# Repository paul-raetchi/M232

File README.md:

# M232
RS-232 => GPIO Level Translator for 6-CH UART monitoring (3xRX + 3xTX). VCC = 3-6V to GND

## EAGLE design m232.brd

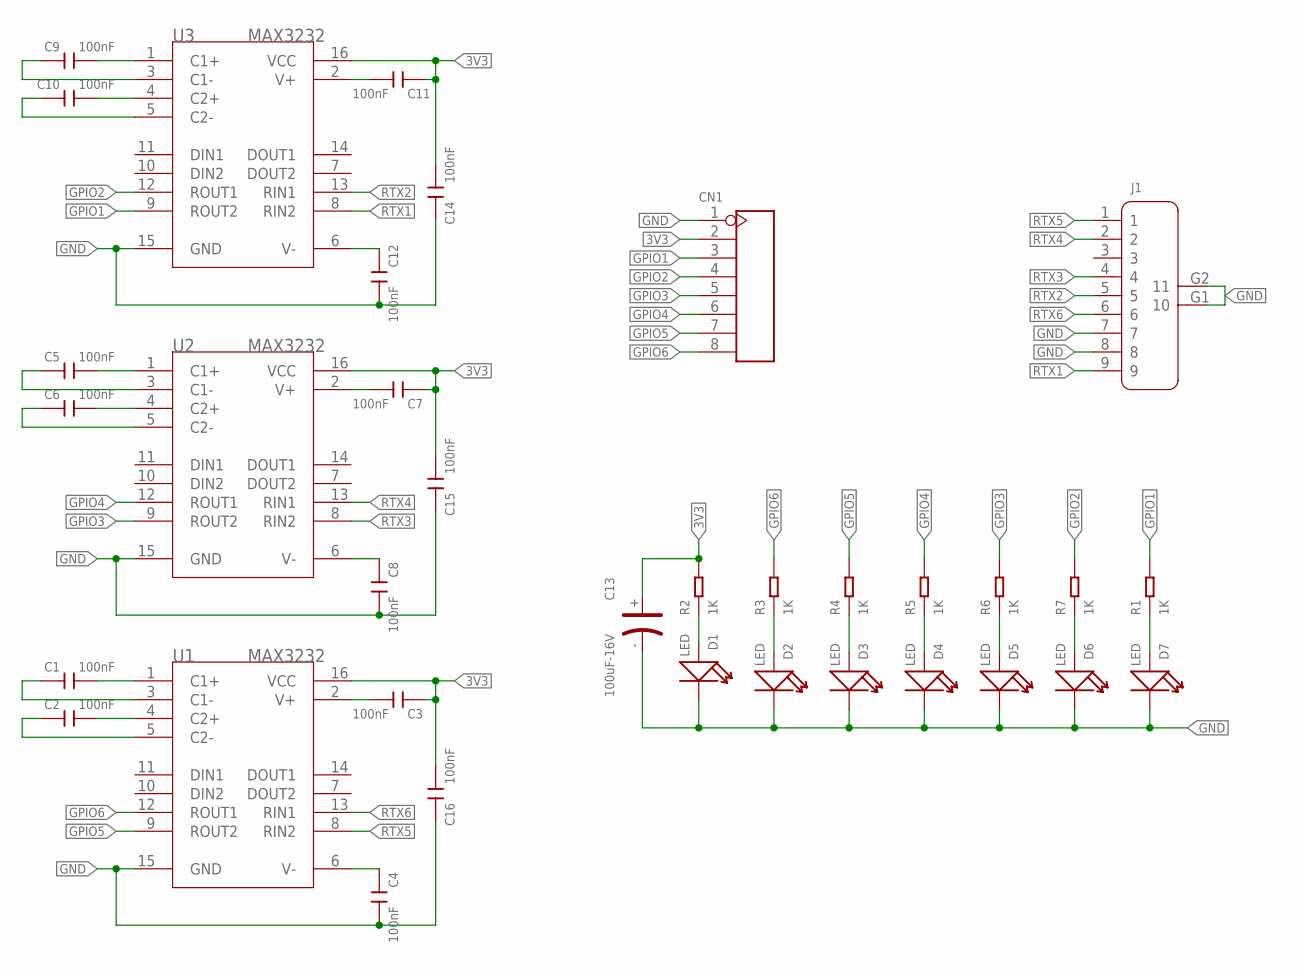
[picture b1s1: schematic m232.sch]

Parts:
C1, C2, C3, C4, C5, C6, C7, C8, C9, C10, C11, C12, C14, C15, C16: 100nF; C0805
C13: 100uF-16V; PC-D5.3MM
CN1: DIP-BLACK-FEMALE-HEADER-VERT(8P); H8-2.54
D1, D2, D3, D4, D5, D6, D7: LED; LED-0805
J1: DIP-MALE-DB9-CONNECTOR; DSUB9+2P-2.77-90D-MALE
R1, R2, R3, R4, R5, R6, R7: 1K; R0805
U1, U2, U3: MAX3232; SOIC16-1.27-10X3.9MM

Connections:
3V3: C3.1, C7.1, C11.1, C13.+, C14.2, C15.2, C16.2, CN1.2, R2.2, U1.16 (VCC), U2.16 (VCC), U3.16 (VCC)
GND: C4.2, C8.2, C12.2, C13.-, C14.1, C15.1, C16.1, CN1.1, D1.-, D2.-, D3.-, D4.-, D5.-, D6.-, D7.-, J1.7, J1.8, J1.G1 (10), J1.G2 (11), U1.15 (GND), U2.15 (GND), U3.15 (GND)
GPIO1: CN1.3, R1.2, U3.9 (ROUT2)
GPIO2: CN1.4, R7.2, U3.12 (ROUT1)
GPIO3: CN1.5, R6.2, U2.9 (ROUT2)
GPIO4: CN1.6, R5.2, U2.12 (ROUT1)
GPIO5: CN1.7, R4.2, U1.9 (ROUT2)
GPIO6: CN1.8, R3.2, U1.12 (ROUT1)
unnamed: C7.2, U2.2 (V+)
unnamed: C5.2, U2.1 (C1+)
unnamed: C3.2, U1.2 (V+)
unnamed: C5.1, U2.3 (C1-)
unnamed: C1.2, U1.1 (C1+)
unnamed: C1.1, U1.3 (C1-)
unnamed: C2.2, U1.4 (C2+)
unnamed: C2.1, U1.5 (C2-)
unnamed: C6.2, U2.4 (C2+)
unnamed: C6.1, U2.5 (C2-)
unnamed: C11.2, U3.2 (V+)
unnamed: C9.2, U3.1 (C1+)
unnamed: C9.1, U3.3 (C1-)
unnamed: C10.2, U3.4 (C2+)
unnamed: C10.1, U3.5 (C2-)
unnamed: D7.+, R1.1
unnamed: D1.+, R2.1
unnamed: D2.+, R3.1
unnamed: D3.+, R4.1
unnamed: D4.+, R5.1
unnamed: D5.+, R6.1
unnamed: D6.+, R7.1
RTX1: J1.9, U3.8 (RIN2)
RTX2: J1.5, U3.13 (RIN1)
RTX3: J1.4, U2.8 (RIN2)
RTX4: J1.2, U2.13 (RIN1)
RTX5: J1.1, U1.8 (RIN2)
RTX6: J1.6, U1.13 (RIN1)
V-: C4.1, U1.6 (V-)
V-1: C8.1, U2.6 (V-)
V-2: C12.1, U3.6 (V-)

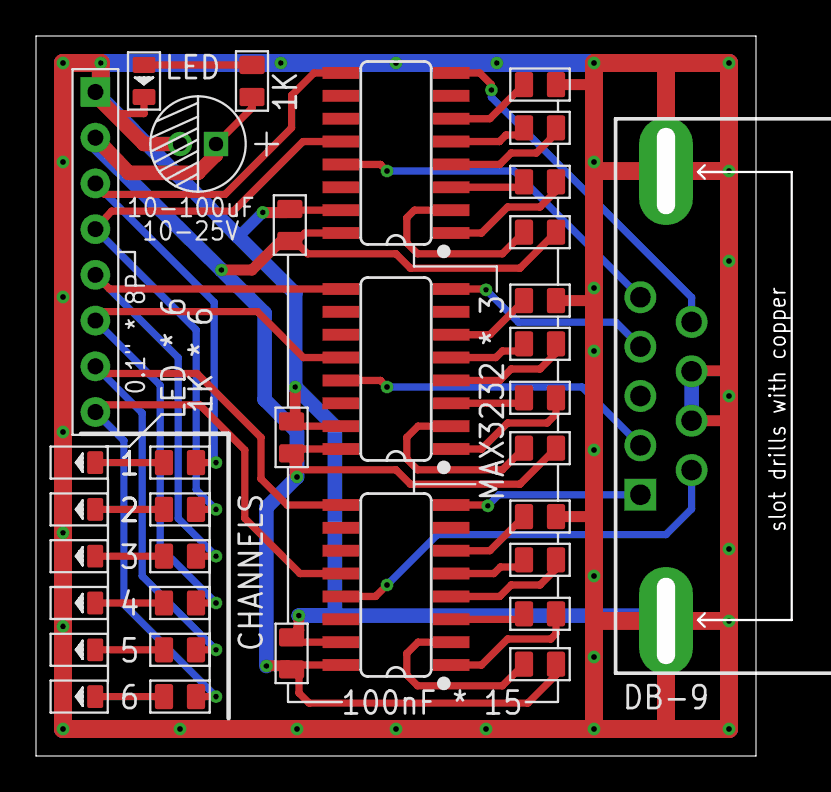
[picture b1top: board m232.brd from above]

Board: 2 copper layers, 42.0 x 40.0 mm, 35 parts (0 on the bottom side), 39 nets.
